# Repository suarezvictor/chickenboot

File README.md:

# ChickenBoot

The unbrickable and versatile embeddable boot loader  

# Building

To build the firmware:  
```
export PICO_SDK_PATH=$HOME/pico/pico-sdk

cd firmware
cmake -S . -B build -DPICO_BOARD=pico
make -C build -j
```

Then copy the build/main.uf2 file to the virtual drive (created by holding the BOOT button, the usual label for the drive is RPI-RP2)
# PCB design files

There are two board designs: one based on a MCU from WCH, the other based on a Raspberry Pi Pico.  

for details, read [Design document](DESIGN.md)

## View the boards online:  
The interactive viewer allows to explore the design in full without the need of installing any tools

- [RPI based design](https://kicanvas.org/?repo=https%3A%2F%2Fgithub.com%2Fsuarezvictor%2Fchickenboot%2Ftree%2Fmain%2Fhardware%2Fchickenboot-rpi)

- [WCH based design](https://kicanvas.org/?repo=https%3A%2F%2Fgithub.com%2Fsuarezvictor%2Fchickenboot%2Ftree%2Fmain%2Fhardware%2Fchickenboot-jtag-wch)

# Licensing
Hardware design files are licensed under the [CERN-OHL-S-2.0](https://opensource.org/license/CERN-OHL-S-2.0) unless otherwise stated.  
Source code is licensed under the [AGPL-3.0](https://opensource.org/license/agpl-3-0) unless otherwise stated.  
  
# Funding
This project is supported by [The Open Source Firmware Foundation](https://www.osfw.foundation/)

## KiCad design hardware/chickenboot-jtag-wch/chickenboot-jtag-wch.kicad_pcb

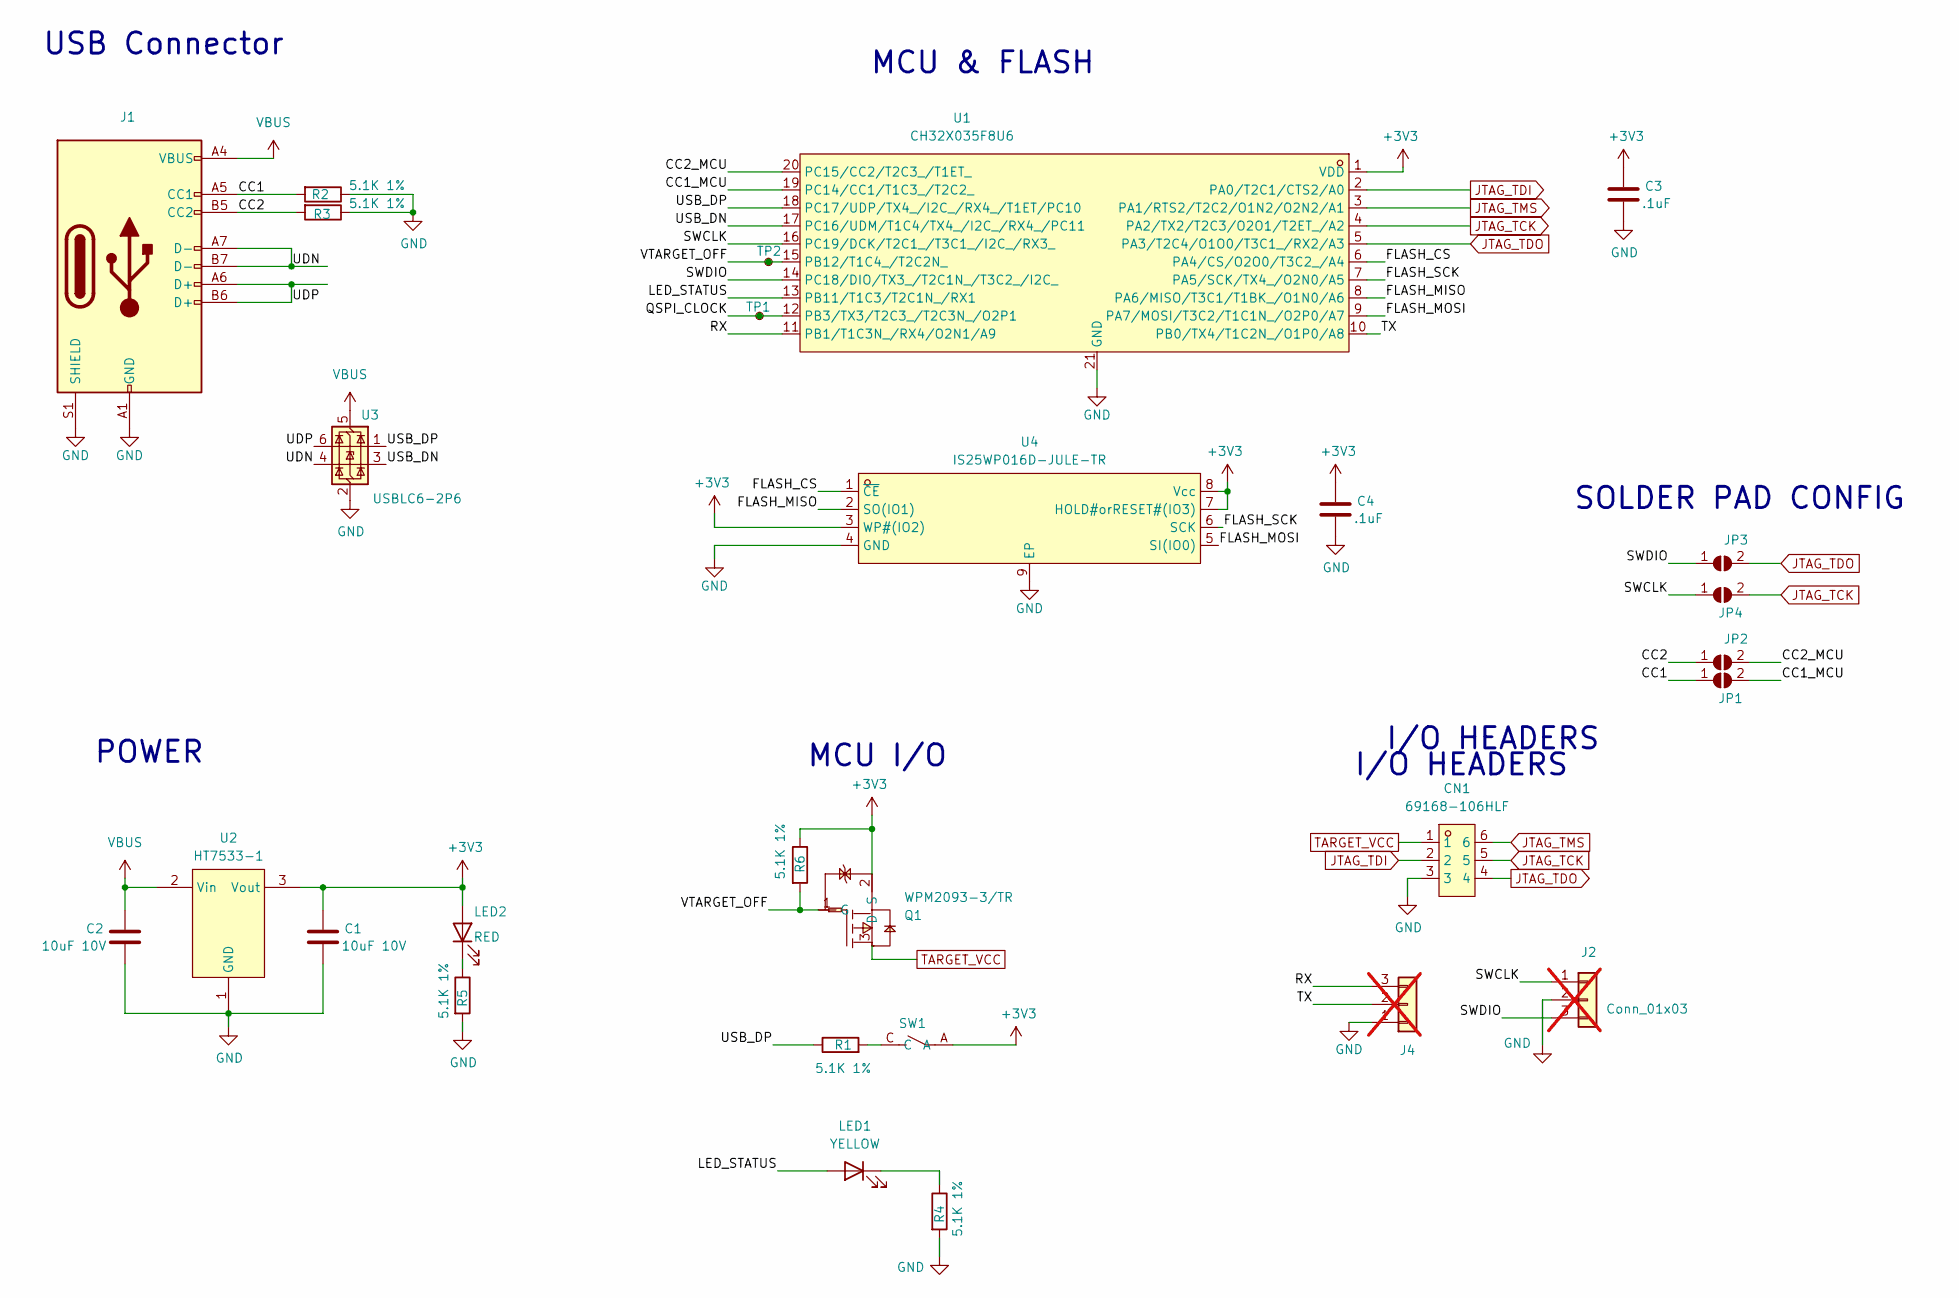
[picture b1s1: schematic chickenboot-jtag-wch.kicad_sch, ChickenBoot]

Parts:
C1, C2: 10uF 10V; C_0805_2012Metric; LCSC Part Number C32635
C3, C4: .1uF; C_0402_1005Metric
CN1: 69168-106HLF; CONN-TH_6P-P2.54_69168-X06; MPN 69168-106HLF; LCSC Part Number C5410110
J1: USB_C_Receptacle_USB2.0; USB_C_Receptacle_G-Switch_GT-USB-7010ASV; MPN GT-USB-7010ASV
J2, J4: Conn_01x03; PinHeader_1x03_P2.54mm_Vertical; not fitted
JP1, JP2, JP3, JP4: SolderJumper_2_Open; SolderJumper-2_P1.3mm_Open_RoundedPad1.0x1.5mm
LED1: YELLOW; LED_0603_1608Metric; MPN XL-1608SURC-04
LED2: RED; LED_0603_1608Metric; MPN XL-1608SURC-06
Q1: WPM2093-3/TR; SOT-723_L1.2-W0.8-P0.80-LS1.2-BR; MPN WPM2093-3/TR; LCSC Part C2931332
R1, R2, R3, R4, R5, R6: 5.1K 1%; R_0402_1005Metric
SW1: SW_Push; SW-SMD_4P-L2.5-W1.6-LS2.9_STI-055A12AX; MPN GT-TC194A-H0055-L1; LCSC Part Number C41398745
TP1, TP2: TestPoint_Small; TestPoint_Pad_1.5x1.5mm
U1: CH32X035F8U6; QFN-20-1EP_3x3mm_P0.4mm_EP1.65x1.65mm_ThermalVias; MPN CH32X035F8U6; LCSC Part Number C42442062
U2: HT7533-1; SOT-89-3; MPN HT7533-1; LCSC Part Number C14289
U3: USBLC6-2P6; SOT-666; MPN USBLC6-2P6; LCSC Part Number C15999
U4: IS25WP016D-JULE-TR; USON-8_L3.0-W2.0-P0.50-BL-EP_IS25LP080D; MPN IS25WP016D-JULE-TR; LCSC Part C2976734

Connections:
+3V3: C1.1, C3.1, C4.1, LED2.2 (A), Q1.2 (S), R6.1, SW1.A, U1.1 (VDD), U2.3 (Vout), U4.3 (WP#(IO2)), U4.7 (HOLD#orRESET#(IO3)), U4.8 (Vcc)
/CC1: J1.A5 (CC1), JP1.1 (A), R2.2
/CC1_MCU: JP1.2 (B), U1.19 (PC14/CC1/T1C3_/T2C2_)
/CC2: J1.B5 (CC2), JP2.1 (A), R3.2
/CC2_MCU: JP2.2 (B), U1.20 (PC15/CC2/T2C3_/T1ET_)
/FLASH_CS: U1.6 (PA4/CS/O2O0/T3C2_/A4), U4.1 (~CE)
/FLASH_MISO: U1.8 (PA6/MISO/T3C1/T1BK_/O1N0/A6), U4.2 (SO(IO1))
/FLASH_MOSI: U1.9 (PA7/MOSI/T3C2/T1C1N_/O2P0/A7), U4.5 (SI(IO0))
/FLASH_SCK: U1.7 (PA5/SCK/TX4_/O2N0/A5), U4.6 (SCK)
/LED_STATUS: LED1.2 (A), U1.13 (PB11/T1C3/T2C1N_/RX1)
/QSPI_CLOCK: TP1.1, U1.12 (PB3/TX3/T2C3_/T2C3N_/O2P1)
/RX: J4.3, U1.11 (PB1/T1C3N_/RX4/O2N1/A9)
/SWCLK: J2.1, JP4.1 (A), U1.16 (PC19/DCK/T2C1_/T3C1_/I2C_/RX3_)
/SWDIO: J2.3, JP3.1 (A), U1.14 (PC18/DIO/TX3_/T2C1N_/T3C2_/I2C_)
/TX: J4.2, U1.10 (PB0/TX4/T1C2N_/O1P0/A8)
/UDN: J1.A7 (D-), J1.B7 (D-), U3.4 (I/O2)
/UDP: J1.A6 (D+), J1.B6 (D+), U3.6 (I/O1)
/USB_DN: U1.17 (PC16/UDM/T1C4/TX4_/I2C_/RX4_/PC11), U3.3 (I/O2)
/USB_DP: R1.1, U1.18 (PC17/UDP/TX4_/I2C_/RX4_/T1ET/PC10), U3.1 (I/O1)
/VTARGET_OFF: Q1.1 (G), R6.2, TP2.1, U1.15 (PB12/T1C4_/T2C2N_)
GND: C1.2, C2.2, C3.2, C4.2, CN1.3, J1.A1 (GND), J1.A12 (GND), J1.B1 (GND), J1.B12 (GND), J1.S1 (SHIELD), J2.2, J4.1, R2.1, R3.1, R4.2, R5.2, U1.21 (GND), U2.1 (GND), U3.2 (GND), U4.4 (GND), U4.9 (EP)
JTAG_TCK: CN1.5, JP4.2 (B), U1.4 (PA2/TX2/T2C3/O2O1/T2ET_/A2)
JTAG_TDI: CN1.2, U1.2 (PA0/T2C1/CTS2/A0)
JTAG_TDO: CN1.4, JP3.2 (B), U1.5 (PA3/T2C4/O1O0/T3C1_/RX2/A3)
JTAG_TMS: CN1.6, U1.3 (PA1/RTS2/T2C2/O1N2/O2N2/A1)
unnamed: LED1.1 (K), R4.1
unnamed: LED2.1 (K), R5.1
unnamed: R1.2, SW1.C
TARGET_VCC: CN1.1, Q1.3 (D)
VBUS: C2.1, J1.A4 (VBUS), J1.A9 (VBUS), J1.B4 (VBUS), J1.B9 (VBUS), U2.2 (Vin), U3.5 (VBUS)

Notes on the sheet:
MCU & FLASH
SOLDER PAD CONFIG
MCU I/O
I/O HEADERS
POWER
USB Connector

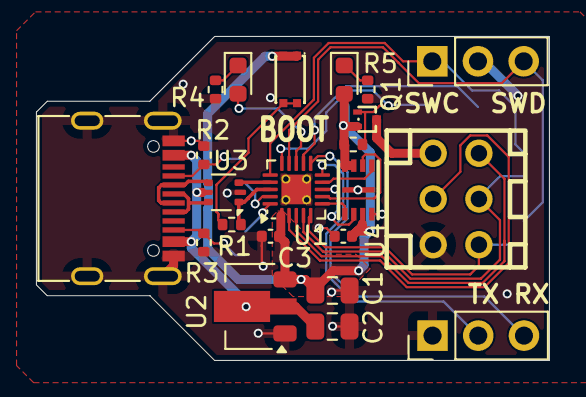
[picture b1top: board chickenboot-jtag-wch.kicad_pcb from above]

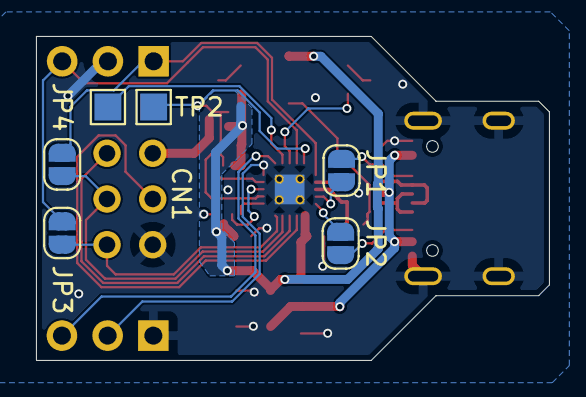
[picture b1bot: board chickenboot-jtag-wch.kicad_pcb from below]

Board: 2 copper layers, 28.5 x 18.0 mm, 28 parts (6 on the bottom side), 30 nets.

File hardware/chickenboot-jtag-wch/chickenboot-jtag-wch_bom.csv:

Comment,Designator,Footprint,LCSC Part Number,MPN,MFG
"10uF 10V","C1,C2",0805,C32635,"",""
"YELLOW","LED1","LED_0603_1608Metric",C965798,"XL-1608SURC-04","XINGLIGHT"
"5.1K 1%","R3,R4,R2,R1,R6,R5",0402,C105872,"RC0402FR-075K1L","YAGEO"
"IS25WP016D-JULE-TR","U4","USON-8_L3.0-W2.0-P0.50-BL-EP_IS25LP080D",C2976734,"IS25WP016D-JULE-TR","ISSI(Integrated Silicon Solution)"
"USB_C_Receptacle_USB2.0","J1","USB_C_Receptacle_G-Switch_GT-USB-7010ASV",C2988369,"GT-USB-7010ASV","G-Switch"
".1uF","C4,C3",0402,C100072,"CL05A104KA5NNNC","Samsung Electro-Mechanics"
"USBLC6-2P6","U3","SOT-666",C15999,"USBLC6-2P6","STMicroelectronics"
"WPM2093-3/TR","Q1","SOT-723_L1.2-W0.8-P0.80-LS1.2-BR",C2931332,"WPM2093-3/TR","WILLSEMI(Will Semicon)"
"69168-106HLF","CN1","CONN-TH_6P-P2.54_69168-X06",C5410110,"69168-106HLF",""
"HT7533-1","U2","SOT-89-3",C14289,"HT7533-1","Holtek Semicon"
"SW_Push","SW1","SW-SMD_4P-L2.5-W1.6-LS2.9_STI-055A12AX",C41398745,"GT-TC194A-H0055-L1",""
"RED","LED2","LED_0603_1608Metric",C965799,"XL-1608SURC-06","XINGLIGHT"
"CH32X035F8U6","U1","QFN-20-1EP_3x3mm_P0.4mm_EP1.65x1.65mm_ThermalVias",C42442062,"CH32X035F8U6","WCH(Jiangsu Qin Heng)"

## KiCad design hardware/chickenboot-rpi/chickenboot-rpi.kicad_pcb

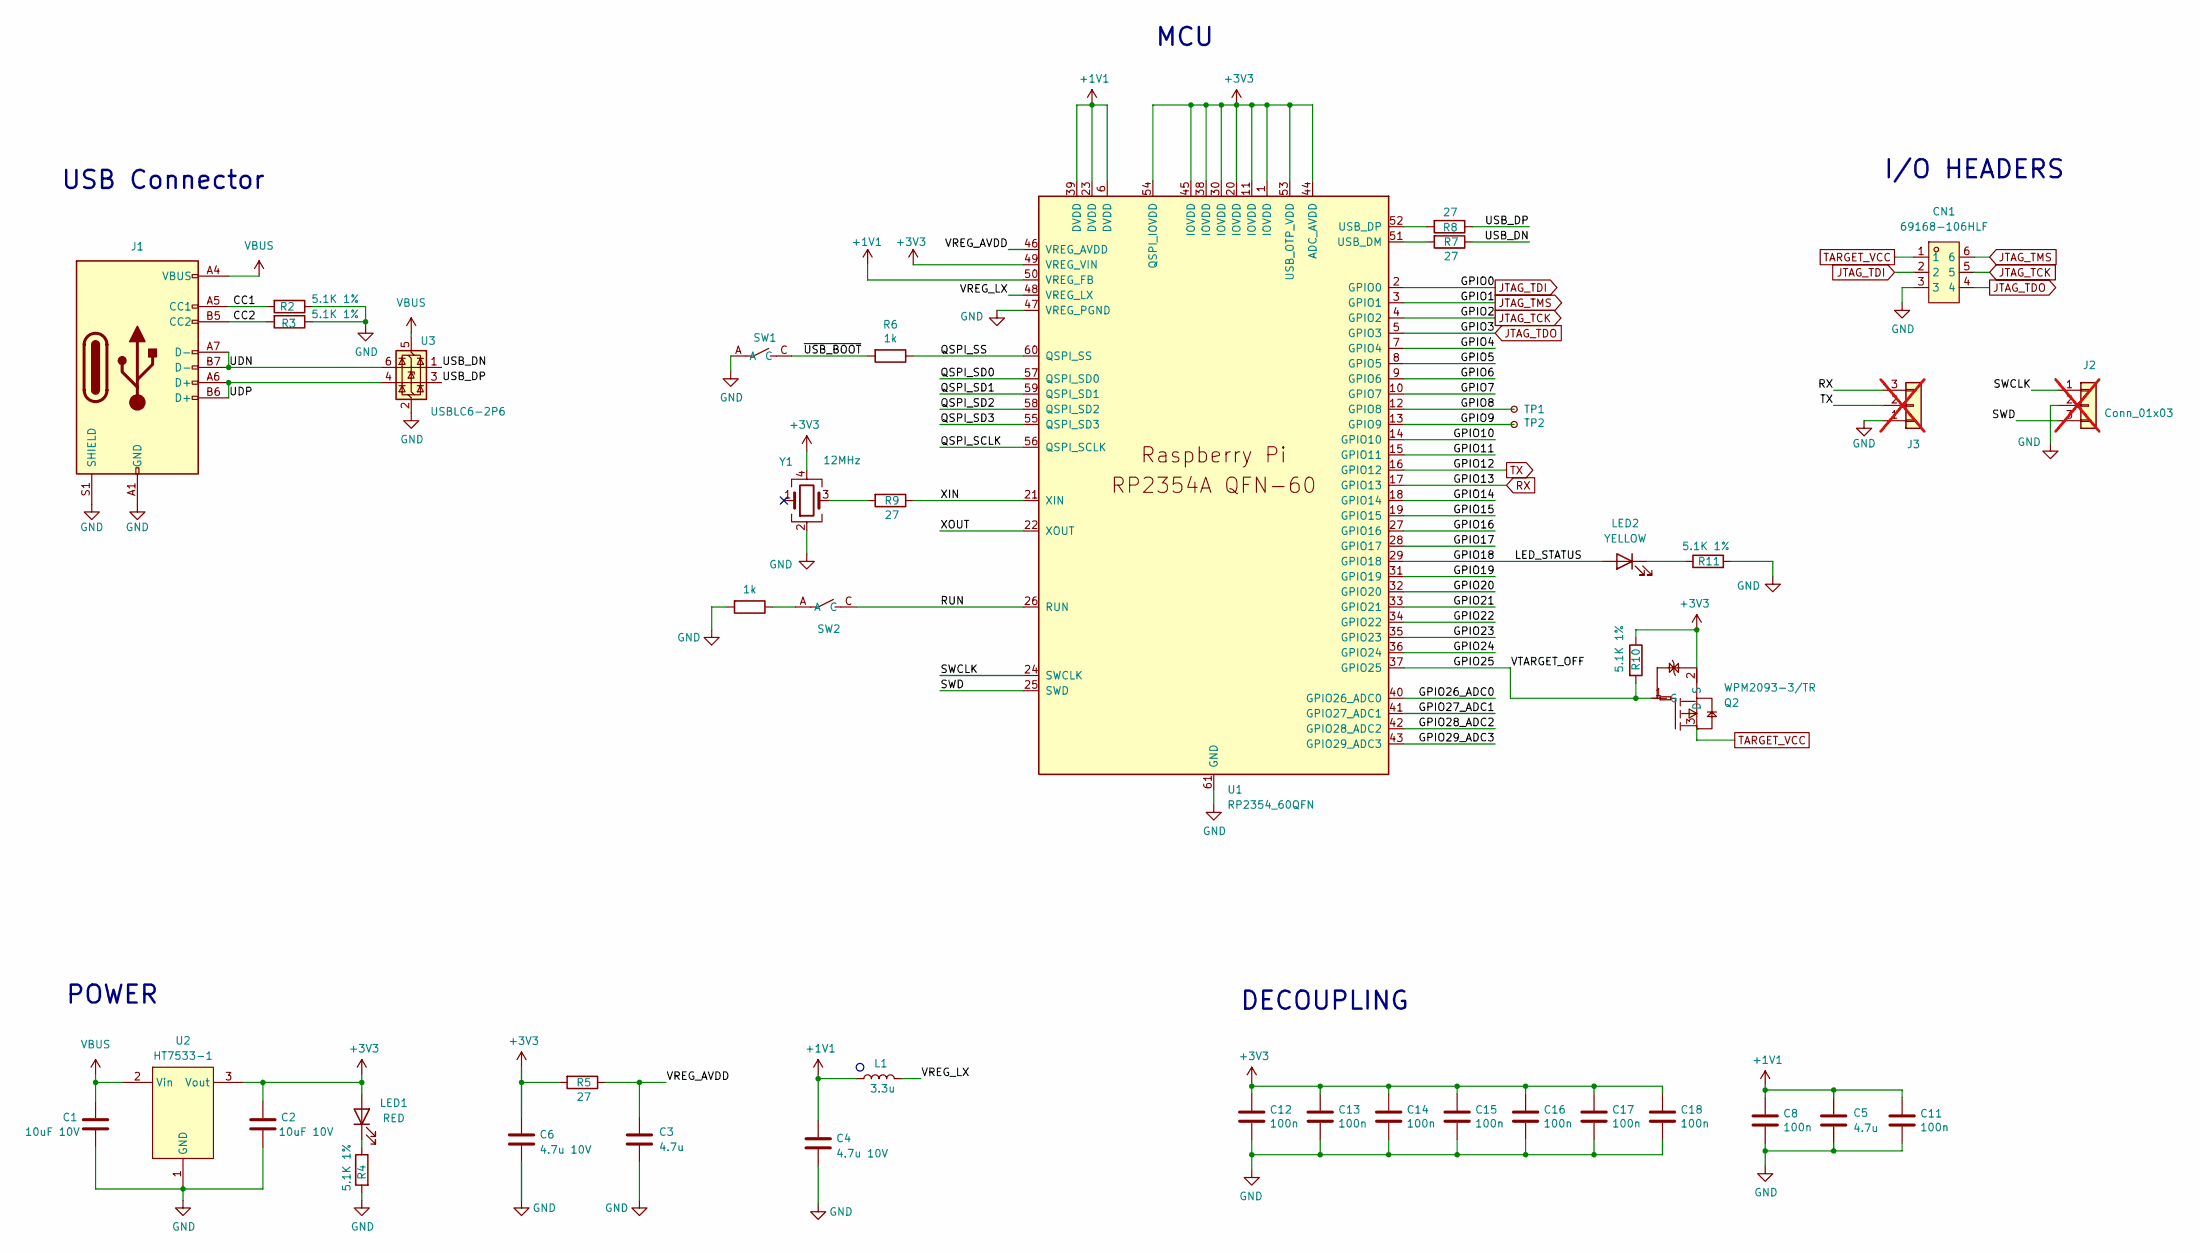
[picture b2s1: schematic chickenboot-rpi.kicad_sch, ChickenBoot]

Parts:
C1, C2: 10uF 10V; C_0805_2012Metric; LCSC Part Number C32635
C3, C5: 4.7u; C_0402_1005Metric_small_pads; MPN CL05A475KP5NRNC
C4, C6: 4.7u 10V; C_0402_1005Metric_small_pads; MPN CL05A475KP5NRNC
C8, C11, C12, C13, C14, C15, C16, C17, C18: 100n; C_0402_1005Metric
CN1: 69168-106HLF; CONN-TH_6P-P2.54_69168-X06; MPN 69168-106HLF; LCSC Part Number C5410110
J1: USB_C_Receptacle_USB2.0; USB_C_Receptacle_G-Switch_GT-USB-7010ASV; MPN GT-USB-7010ASV
J2, J3: Conn_01x03; PinHeader_1x03_P2.54mm_Vertical; not fitted
L1: 3.3u; L_pol_2016; MPN AOTA-B201610S3R3-101-T; LCSC Part Number C42411119
LED1: RED; LED_0603_1608Metric; MPN XL-1608SURC-06
LED2: YELLOW; LED_0603_1608Metric; MPN XL-1608SURC-04
Q2: WPM2093-3/TR; SOT-723_L1.2-W0.8-P0.80-LS1.2-BR; MPN WPM2093-3/TR; LCSC Part C2931332
R1, R6: 1k; R_0402_1005Metric
R2, R3, R4, R10, R11: 5.1K 1%; R_0402_1005Metric
R5, R7, R8, R9: 27; R_0402_1005Metric
SW1, SW2: SW_Push; SW-SMD_4P-L2.5-W1.6-LS2.9_STI-055A12AX; MPN GT-TC194A-H0055-L1; LCSC Part Number C41398745
TP1, TP2: TestPoint_Small; TestPoint_Pad_1.5x1.5mm
U1: RP2354_60QFN; RP2350-QFN-60-1EP_7x7_P0.4mm_EP3.4x3.4mm_ThermalVias; MPN RP2354A; LCSC Part Number C41378174
U2: HT7533-1; SOT-89-3; MPN HT7533-1; LCSC Part Number C14289
U3: USBLC6-2P6; SOT-666; MPN USBLC6-2P6; LCSC Part Number C15999
Y1: 12MHz; OSC-SMD_4P-L2.0-W1.6-BL_8NE; MPN YE12MUBCE2O; LCSC Part Number C54307921

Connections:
+1V1: C4.1, C5.1, C8.1, C11.1, L1.1, U1.6 (DVDD), U1.23 (DVDD), U1.39 (DVDD), U1.50 (VREG_FB)
+3V3: C2.1, C6.1, C12.1, C13.1, C14.1, C15.1, C16.1, C17.1, C18.1, LED1.2 (A), Q2.2 (S), R5.2, R10.1, U1.1 (IOVDD), U1.11 (IOVDD), U1.20 (IOVDD), U1.30 (IOVDD), U1.38 (IOVDD), U1.44 (ADC_AVDD), U1.45 (IOVDD), U1.49 (VREG_VIN), U1.53 (USB_OTP_VDD), U1.54 (QSPI_IOVDD), U2.3 (Vout), Y1.4
/CC1: J1.A5 (CC1), R2.2
/CC2: J1.B5 (CC2), R3.2
/GPIO4: U1.7 (GPIO4)
/GPIO5: U1.8 (GPIO5)
/GPIO6: U1.9 (GPIO6)
/GPIO7: U1.10 (GPIO7)
/GPIO8: TP1.1, U1.12 (GPIO8)
/GPIO9: TP2.1, U1.13 (GPIO9)
/GPIO10: U1.14 (GPIO10)
/GPIO11: U1.15 (GPIO11)
/GPIO14: U1.18 (GPIO14)
/GPIO15: U1.19 (GPIO15)
/GPIO16: U1.27 (GPIO16)
/GPIO17: U1.28 (GPIO17)
/GPIO18: LED2.2 (A), U1.29 (GPIO18)
/GPIO19: U1.31 (GPIO19)
/GPIO20: U1.32 (GPIO20)
/GPIO21: U1.33 (GPIO21)
/GPIO22: U1.34 (GPIO22)
/GPIO23: U1.35 (GPIO23)
/GPIO24: U1.36 (GPIO24)
/GPIO25: Q2.1 (G), R10.2, U1.37 (GPIO25)
/GPIO26_ADC0: U1.40 (GPIO26_ADC0)
/GPIO27_ADC1: U1.41 (GPIO27_ADC1)
/GPIO28_ADC2: U1.42 (GPIO28_ADC2)
/GPIO29_ADC3: U1.43 (GPIO29_ADC3)
/QSPI_SCLK: U1.56 (QSPI_SCLK)
/QSPI_SD0: U1.57 (QSPI_SD0)
/QSPI_SD1: U1.59 (QSPI_SD1)
/QSPI_SD2: U1.58 (QSPI_SD2)
/QSPI_SD3: U1.55 (QSPI_SD3)
/QSPI_SS: R6.1, U1.60 (QSPI_SS)
/RUN: SW2.C, U1.26 (RUN)
/SWCLK: J2.1, U1.24 (SWCLK)
/SWD: J2.3, U1.25 (SWD)
/UDN: J1.A7 (D-), J1.B7 (D-), U3.6 (I/O1)
/UDP: J1.A6 (D+), J1.B6 (D+), U3.4 (I/O2)
/USB_DN: R7.1, U3.1 (I/O1)
/USB_DP: R8.1, U3.3 (I/O2)
/VREG_AVDD: C3.1, R5.1, U1.46 (VREG_AVDD)
/VREG_LX: L1.2, U1.48 (VREG_LX)
/XIN: R9.1, U1.21 (XIN)
/XOUT: U1.22 (XOUT)
/~USB_BOOT: R6.2, SW1.C
GND: C1.2, C2.2, C3.2, C4.2, C5.2, C6.2, C8.2, C11.2, C12.2, C13.2, C14.2, C15.2, C16.2, C17.2, C18.2, CN1.3, J1.A1 (GND), J1.A12 (GND), J1.B1 (GND), J1.B12 (GND), J1.S1 (SHIELD), J2.2, J3.1, R1.2, R2.1, R3.1, R4.2, R11.2, SW1.A, U1.47 (VREG_PGND), U1.61 (GND), U2.1 (GND), U3.2 (GND), Y1.2
JTAG_TCK: CN1.5, U1.4 (GPIO2)
JTAG_TDI: CN1.2, U1.2 (GPIO0)
JTAG_TDO: CN1.4, U1.5 (GPIO3)
JTAG_TMS: CN1.6, U1.3 (GPIO1)
unnamed: LED1.1 (K), R4.1
unnamed: LED2.1 (K), R11.1
unnamed: R1.1, SW2.A
unnamed: R9.2, Y1.3
unnamed: R7.2, U1.51 (USB_DM)
unnamed: R8.2, U1.52 (USB_DP)
RX: J3.3, U1.17 (GPIO13)
TARGET_VCC: CN1.1, Q2.3 (D)
TX: J3.2, U1.16 (GPIO12)
VBUS: C1.1, J1.A4 (VBUS), J1.A9 (VBUS), J1.B4 (VBUS), J1.B9 (VBUS), U2.2 (Vin), U3.5 (VBUS)

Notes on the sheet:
USB Connector
POWER
MCU
DECOUPLING
I/O HEADERS

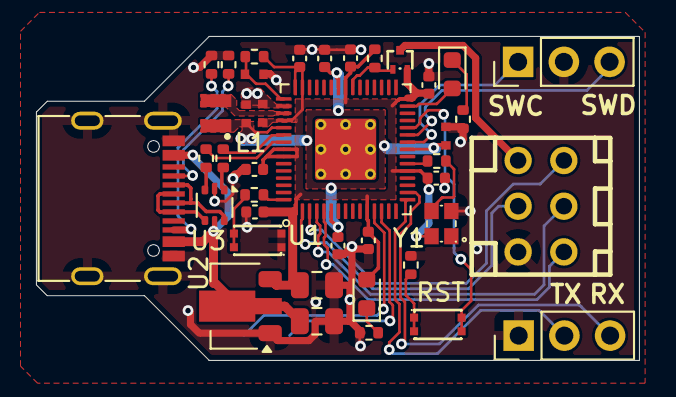
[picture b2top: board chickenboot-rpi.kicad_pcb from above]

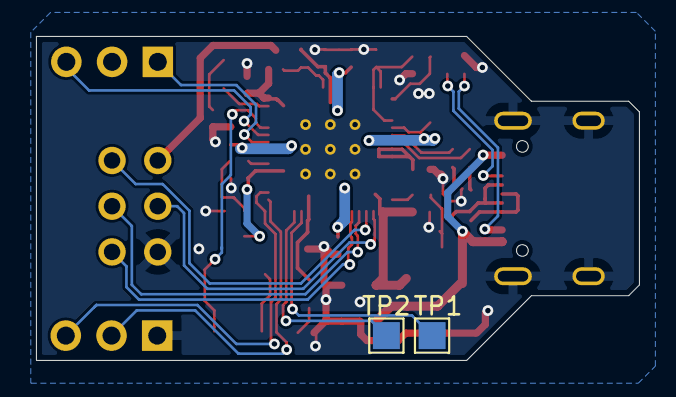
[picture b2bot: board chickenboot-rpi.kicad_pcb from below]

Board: 2 copper layers, 33.5 x 18.0 mm, 42 parts (2 on the bottom side), 35 nets.

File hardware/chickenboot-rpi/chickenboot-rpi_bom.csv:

Comment,Designator,Footprint,LCSC Part Number,MPN,MFG
"100n","C18,C16,C14,C11,C8,C15,C13,C12,C17",0402,C100072,"CL05A104KA5NNNC","Samsung Electro-Mechanics"
"1k","R1,R6",0402,C105637,"RC0402JR-071KL","YAGEO"
"69168-106HLF","CN1","CONN-TH_6P-P2.54_69168-X06",C5410110,"69168-106HLF",""
"3.3u","L1","L_pol_2016",C42411119,"AOTA-B201610S3R3-101-T",""
"10uF 10V","C1,C2",0805,C32635,"",""
"27","R5,R8,R7,R9",0402,C25100,"0402WGF270JTCE","UNI-ROYAL(Uniroyal Elec)"
"RP2350_60QFN","U1","RP2350-QFN-60-1EP_7x7_P0.4mm_EP3.4x3.4mm_ThermalVias",C41378174,"RP2354A",""
"4.7u 10V","C5,C6,C3,C4","C_0402_1005Metric_small_pads",C368809,"CL05A475KP5NRNC","Samsung Electro-Mechanics"
"YELLOW","LED2","LED_0603_1608Metric",C965798,"XL-1608SURC-04","XINGLIGHT"
"5.1K 1%","R10,R11,R2,R4,R3",0402,C105872,"RC0402FR-075K1L","YAGEO"
"HT7533-1","U2","SOT-89-3",C14289,"HT7533-1","Holtek Semicon"
"USB_C_Receptacle_USB2.0","J1","USB_C_Receptacle_G-Switch_GT-USB-7010ASV",C2988369,"GT-USB-7010ASV","G-Switch"
"SW_Push","SW1,SW2","SW-SMD_4P-L2.5-W1.6-LS2.9_STI-055A12AX",C41398745,"GT-TC194A-H0055-L1",""
"WPM2093-3/TR","Q2","SOT-723_L1.2-W0.8-P0.80-LS1.2-BR",C2931332,"WPM2093-3/TR","WILLSEMI(Will Semicon)"
"RED","LED1","LED_0603_1608Metric",C965799,"XL-1608SURC-06","XINGLIGHT"
"12MHz","Y1","OSC-SMD_4P-L2.0-W1.6-BL_8NE",C54307921,"YE12MUBCE2O",""
"USBLC6-2P6","U3","SOT-666",C15999,"USBLC6-2P6","STMicroelectronics"

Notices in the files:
hardware/chickenboot-jtag-wch/chickenboot-jtag-wch.kicad_sch:
(C) 2026 Victor Suarez Rovere
